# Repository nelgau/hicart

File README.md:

# Home Invader 64

This is a present for an old friend!

## Prerequisites

Get these taps:

    $ brew tap nelgau/fpga
    $ brew tap riscv-software-src/riscv

Install the following packages:

    $ brew install --HEAD yosys
    $ brew install --HEAD nelgau/fpga/nextpnr-ecp5
    $ brew install --HEAD nelgau/fpga/ecpprog
    $ brew install riscv-software-src/riscv/riscv-tools
    $ brew install icarus-verilog

Note: Building `nextpnr-ecp5` takes approximately 11 minutes on an M1 MacBook Pro.

Build a recent Python with shared object support (for cocotb) using pyenv:

    $ PYTHON_CONFIGURE_OPTS="--enable-shared" pyenv install 3.10.6

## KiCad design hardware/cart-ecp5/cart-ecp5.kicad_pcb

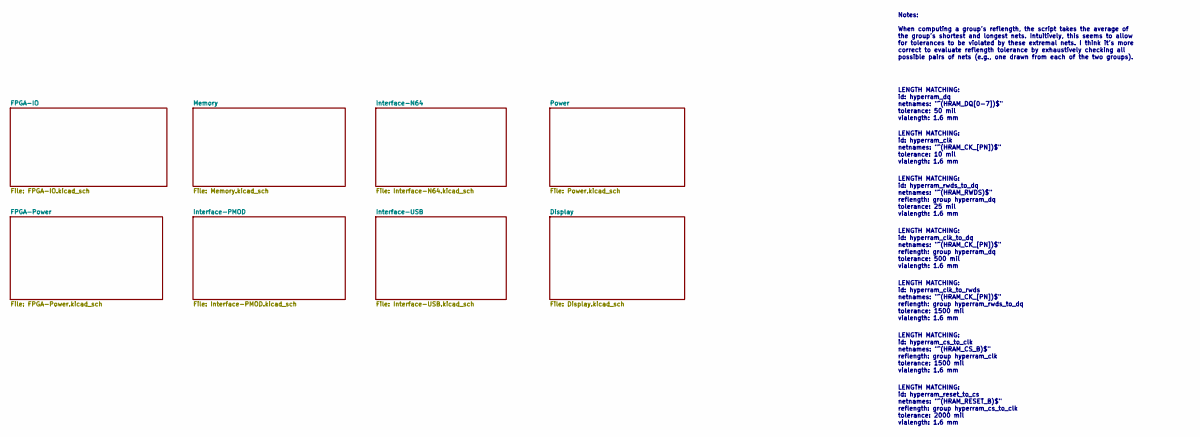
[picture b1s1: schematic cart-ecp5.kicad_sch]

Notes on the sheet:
LENGTH MATCHING: id: hyperram_reset_to_cs netnames: "^(HRAM_RESET_B)$" reflength: group hyperram_cs_to_clk tolerance: 2000 mil vialength: 1.6 mm
LENGTH MATCHING: id: hyperram_clk_to_dq netnames: "^(HRAM_CK_[PN])$" reflength: group hyperram_dq tolerance: 500 mil vialength: 1.6 mm
LENGTH MATCHING: id: hyperram_clk netnames: "^(HRAM_CK_[PN])$" tolerance: 10 mil vialength: 1.6 mm
LENGTH MATCHING: id: hyperram_dq netnames: "^(HRAM_DQ[0-7])$" tolerance: 50 mil vialength: 1.6 mm
LENGTH MATCHING: id: hyperram_clk_to_rwds netnames: "^(HRAM_CK_[PN])$" reflength: group hyperram_rwds_to_dq tolerance: 1500 mil vialength: 1.6 mm
LENGTH MATCHING: id: hyperram_cs_to_clk netnames: "^(HRAM_CS_B)$" reflength: group hyperram_clk tolerance: 1500 mil vialength: 1.6 mm
LENGTH MATCHING: id: hyperram_rwds_to_dq netnames: "^(HRAM_RWDS)$" reflength: group hyperram_dq tolerance: 25 mil vialength: 1.6 mm
Notes: When computing a group's reflength, the script takes the average of the group's shortest and longest nets. Intuitively, this seems to allow for tolerances to be violated by these extremal nets. I think it's more correct to evaluate reflength tolerance by exhaustively checking all possible pa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

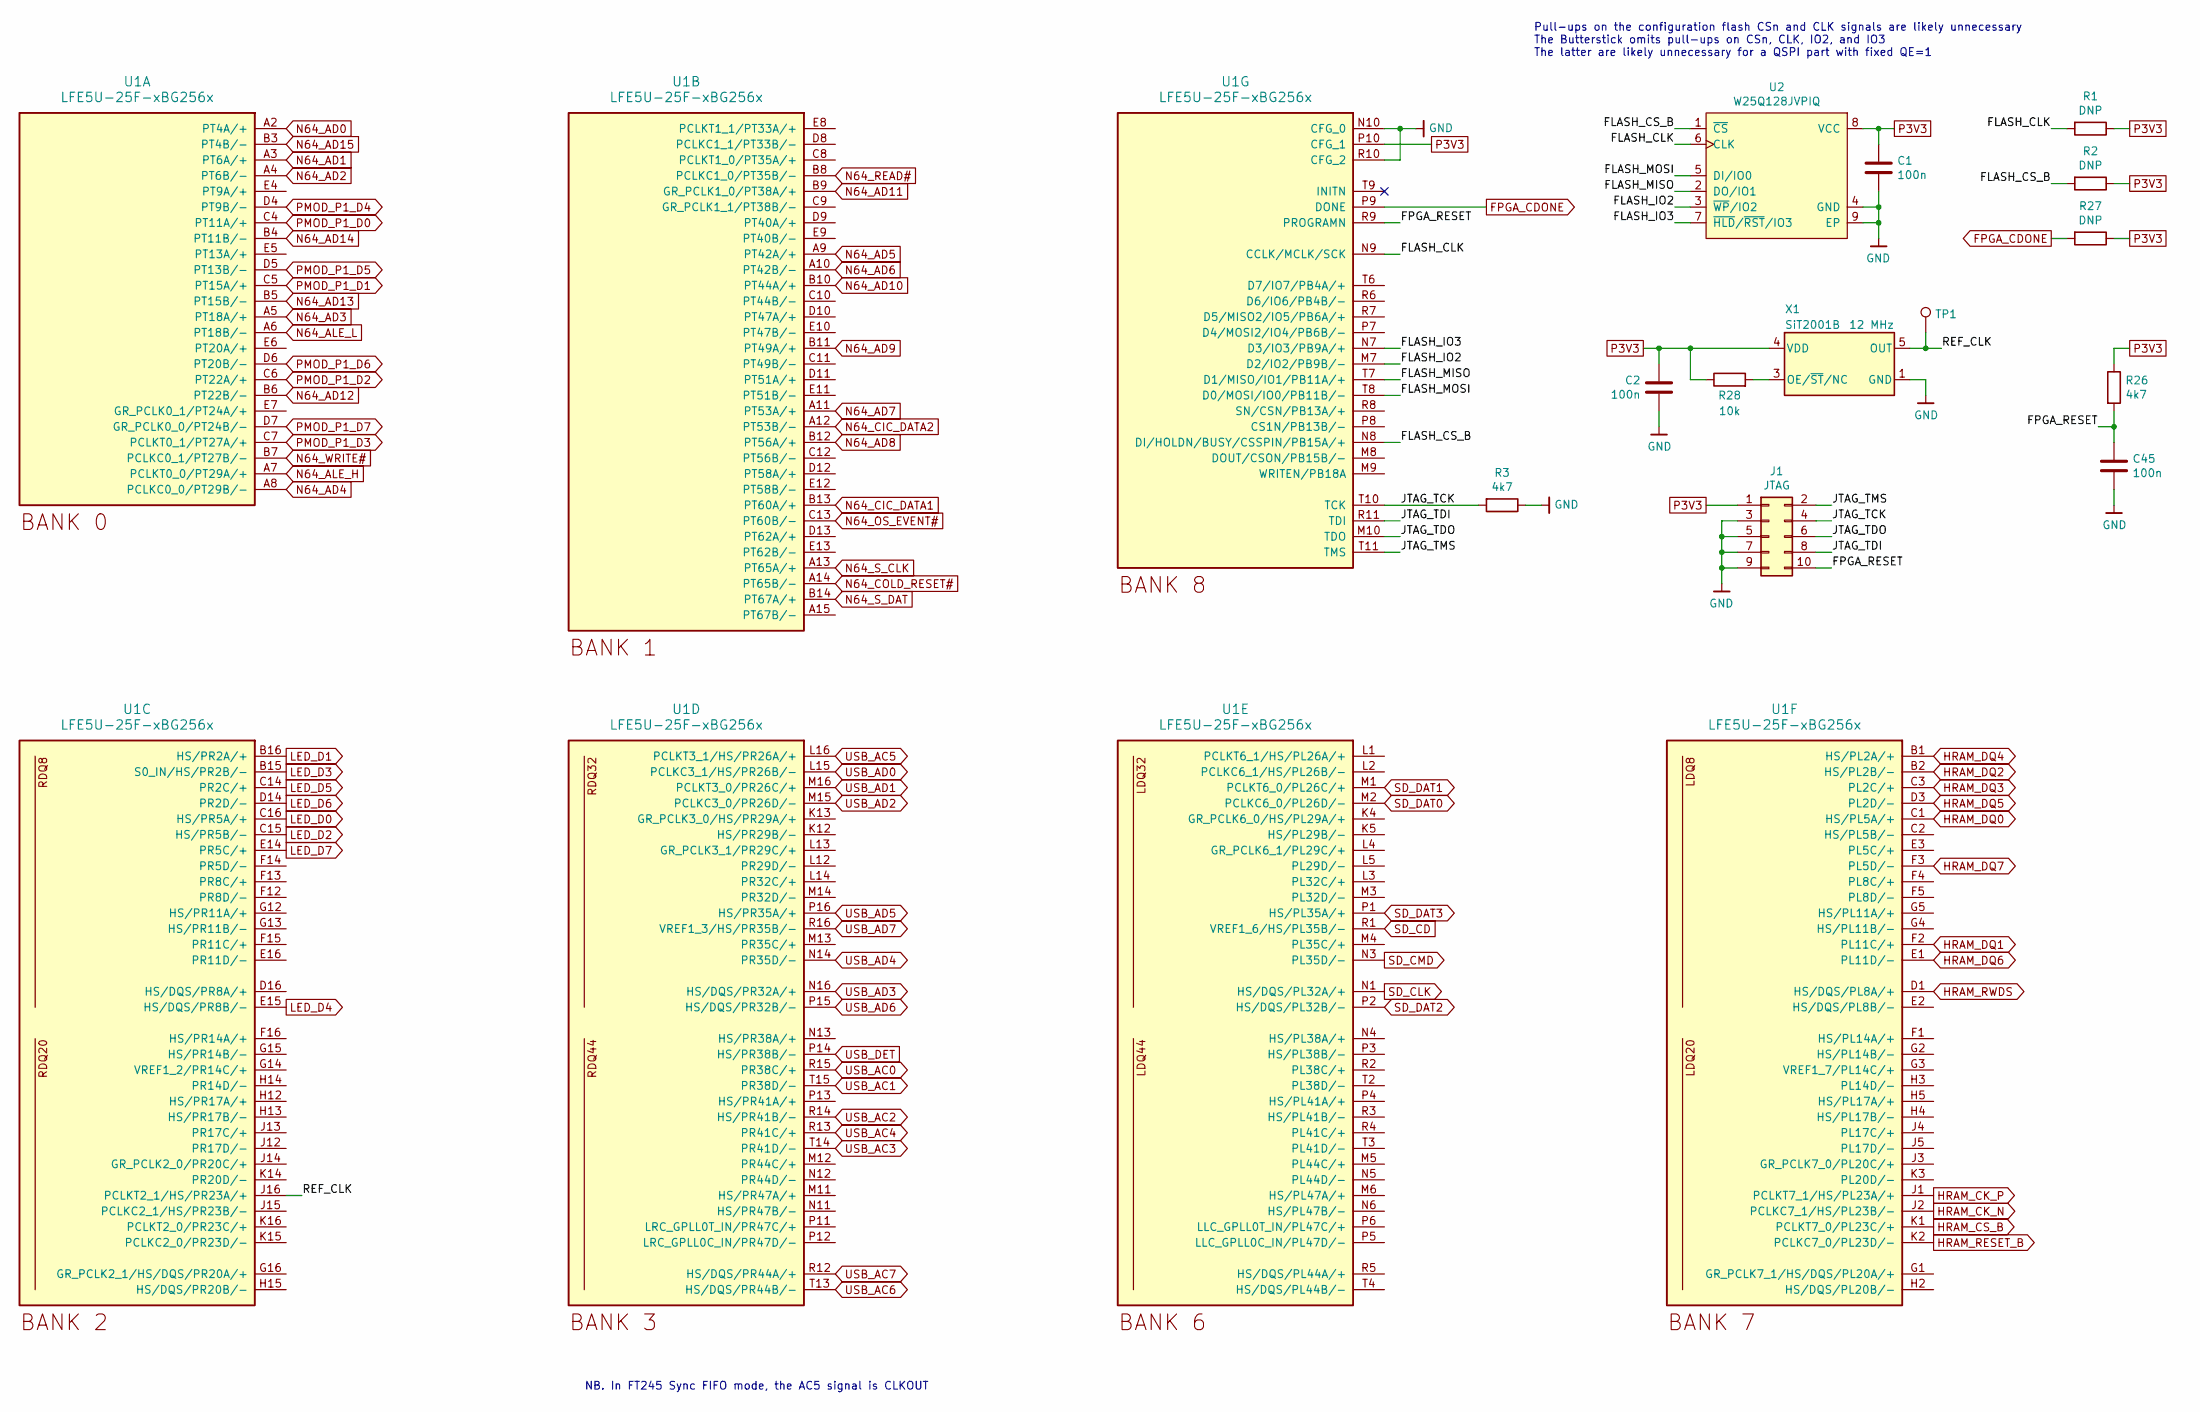
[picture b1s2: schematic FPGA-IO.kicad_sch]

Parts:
C1, C2, C45: 100n; C_0402_1005Metric; MPN CL05B104KO5NNNC
J1: JTAG; Samtec_FTSH-105-XX-X-DV-Mating; MPN FTSH-105-01-L-DV-K
R1, R2, R27: DNP; R_0402_1005Metric
R3, R26: 4k7; R_0402_1005Metric; MPN RC0402FR-074K7L
R28: 10k; R_0402_1005Metric; MPN RC0402FR-0710KL
TP1: TestPoint; TestPoint_Pad_D1.0mm
U1: LFE5U-25F-xBG256x; LFE5U-25F_BGA-256_14.0x14.0mm_Layout16x16_P0.8mm_Pad0.35mm; MPN LFE5U-25F-xBG256x
U2: W25Q128JVPIQ; WSON-8-1EP_6x5mm_P1.27mm_EP3.4x4mm; MPN W25Q128JVPIQ
X1: SiT2001B; SOT-23-5; MPN SiT2001BI-S2-33E-12.000000G

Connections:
/FPGA-IO/FLASH_CLK: R1.2, U1.N9 (CCLK/MCLK/SCK), U2.6 (CLK)
/FPGA-IO/FLASH_CS_B: R2.2, U1.N8 (DI/HOLDN/BUSY/CSSPIN/PB15A/+), U2.1 (~CS)
/FPGA-IO/FLASH_IO2: U1.M7 (D2/IO2/PB9B/-), U2.3 (~WP/IO2)
/FPGA-IO/FLASH_IO3: U1.N7 (D3/IO3/PB9A/+), U2.7 (~HLD/~RST/IO3)
/FPGA-IO/FLASH_MISO: U1.T7 (D1/MISO/IO1/PB11A/+), U2.2 (DO/IO1)
/FPGA-IO/FLASH_MOSI: U1.T8 (D0/MOSI/IO0/PB11B/-), U2.5 (DI/IO0)
/FPGA-IO/FPGA_RESET: C45.1, J1.10, R26.2, U1.R9 (PROGRAMN)
/FPGA-IO/JTAG_TCK: J1.4, R3.2, U1.T10 (TCK)
/FPGA-IO/JTAG_TDI: J1.8, U1.R11 (TDI)
/FPGA-IO/JTAG_TDO: J1.6, U1.M10 (TDO)
/FPGA-IO/JTAG_TMS: J1.2, U1.T11 (TMS)
/FPGA-IO/REF_CLK: TP1.1, U1.J16 (PCLKT2_1/HS/PR23A/+), X1.5 (OUT)
FPGA_CDONE: R27.2, U1.P9 (DONE); also elsewhere on the board
GND: C1.2, C2.2, C45.2, J1.3, J1.5, J1.7, J1.9, R3.1, U1.N10 (CFG_0), U1.R10 (CFG_2), U2.4 (GND), U2.9 (EP), X1.1 (GND); also elsewhere on the board
HRAM_CK_N: U1.J2 (PCLKC7_1/HS/PL23B/-); also elsewhere on the board
HRAM_CK_P: U1.J1 (PCLKT7_1/HS/PL23A/+); also elsewhere on the board
HRAM_CS_B: U1.K1 (PCLKT7_0/PL23C/+); also elsewhere on the board
HRAM_DQ0: U1.C1 (HS/PL5A/+); also elsewhere on the board
HRAM_DQ1: U1.F2 (PL11C/+); also elsewhere on the board
HRAM_DQ2: U1.B2 (HS/PL2B/-); also elsewhere on the board
HRAM_DQ3: U1.C3 (PL2C/+); also elsewhere on the board
HRAM_DQ4: U1.B1 (HS/PL2A/+); also elsewhere on the board
HRAM_DQ5: U1.D3 (PL2D/-); also elsewhere on the board
HRAM_DQ6: U1.E1 (PL11D/-); also elsewhere on the board
HRAM_DQ7: U1.F3 (PL5D/-); also elsewhere on the board
HRAM_RESET_B: U1.K2 (PCLKC7_0/PL23D/-); also elsewhere on the board
HRAM_RWDS: U1.D1 (HS/DQS/PL8A/+); also elsewhere on the board
LED_D0: U1.C16 (HS/PR5A/+); also elsewhere on the board
LED_D1: U1.B16 (HS/PR2A/+); also elsewhere on the board
LED_D2: U1.C15 (HS/PR5B/-); also elsewhere on the board
LED_D3: U1.B15 (S0_IN/HS/PR2B/-); also elsewhere on the board
LED_D4: U1.E15 (HS/DQS/PR8B/-); also elsewhere on the board
LED_D5: U1.C14 (PR2C/+); also elsewhere on the board
LED_D6: U1.D14 (PR2D/-); also elsewhere on the board
LED_D7: U1.E14 (PR5C/+); also elsewhere on the board
N64_AD0: U1.A2 (PT4A/+); also elsewhere on the board
N64_AD1: U1.A3 (PT6A/+); also elsewhere on the board
N64_AD2: U1.A4 (PT6B/-); also elsewhere on the board
N64_AD3: U1.A5 (PT18A/+); also elsewhere on the board
N64_AD4: U1.A8 (PCLKC0_0/PT29B/-); also elsewhere on the board
N64_AD5: U1.A9 (PT42A/+); also elsewhere on the board
N64_AD6: U1.A10 (PT42B/-); also elsewhere on the board
N64_AD7: U1.A11 (PT53A/+); also elsewhere on the board
N64_AD8: U1.B12 (PT56A/+); also elsewhere on the board
N64_AD9: U1.B11 (PT49A/+); also elsewhere on the board
N64_AD10: U1.B10 (PT44A/+); also elsewhere on the board
N64_AD11: U1.B9 (GR_PCLK1_0/PT38A/+); also elsewhere on the board
N64_AD12: U1.B6 (PT22B/-); also elsewhere on the board
N64_AD13: U1.B5 (PT15B/-); also elsewhere on the board
N64_AD14: U1.B4 (PT11B/-); also elsewhere on the board
N64_AD15: U1.B3 (PT4B/-); also elsewhere on the board
N64_ALE_H: U1.A7 (PCLKT0_0/PT29A/+); also elsewhere on the board
N64_ALE_L: U1.A6 (PT18B/-); also elsewhere on the board
N64_CIC_DATA1: U1.B13 (PT60A/+); also elsewhere on the board
N64_CIC_DATA2: U1.A12 (PT53B/-); also elsewhere on the board
N64_COLD_RESET#: U1.A14 (PT65B/-); also elsewhere on the board
N64_OS_EVENT#: U1.C13 (PT60B/-); also elsewhere on the board
N64_READ#: U1.B8 (PCLKC1_0/PT35B/-); also elsewhere on the board
N64_S_CLK: U1.A13 (PT65A/+); also elsewhere on the board
N64_S_DAT: U1.B14 (PT67A/+); also elsewhere on the board
N64_WRITE#: U1.B7 (PCLKC0_1/PT27B/-); also elsewhere on the board
unnamed: R28.2, X1.3 (OE/~ST/NC)
P3V3: C1.1, C2.1, J1.1, R1.1, R2.1, R26.1, R27.1, R28.1, U1.P10 (CFG_1), U2.8 (VCC), X1.4 (VDD); also elsewhere on the board
PMOD_P1_D0: U1.C4 (PT11A/+); also elsewhere on the board
PMOD_P1_D1: U1.C5 (PT15A/+); also elsewhere on the board
PMOD_P1_D2: U1.C6 (PT22A/+); also elsewhere on the board
PMOD_P1_D3: U1.C7 (PCLKT0_1/PT27A/+); also elsewhere on the board
PMOD_P1_D4: U1.D4 (PT9B/-); also elsewhere on the board
PMOD_P1_D5: U1.D5 (PT13B/-); also elsewhere on the board
PMOD_P1_D6: U1.D6 (PT20B/-); also elsewhere on the board
PMOD_P1_D7: U1.D7 (GR_PCLK0_0/PT24B/-); also elsewhere on the board
SD_CD: U1.R1 (VREF1_6/HS/PL35B/-); also elsewhere on the board
SD_CLK: U1.N1 (HS/DQS/PL32A/+); also elsewhere on the board
SD_CMD: U1.N3 (PL35D/-); also elsewhere on the board
SD_DAT0: U1.M2 (PCLKC6_0/PL26D/-); also elsewhere on the board
SD_DAT1: U1.M1 (PCLKT6_0/PL26C/+); also elsewhere on the board
SD_DAT2: U1.P2 (HS/DQS/PL32B/-); also elsewhere on the board
SD_DAT3: U1.P1 (HS/PL35A/+); also elsewhere on the board
USB_AC0: U1.R15 (PR38C/+); also elsewhere on the board
USB_AC1: U1.T15 (PR38D/-); also elsewhere on the board
USB_AC2: U1.R14 (HS/PR41B/-); also elsewhere on the board
USB_AC3: U1.T14 (PR41D/-); also elsewhere on the board
USB_AC4: U1.R13 (PR41C/+); also elsewhere on the board
USB_AC5: U1.L16 (PCLKT3_1/HS/PR26A/+); also elsewhere on the board
USB_AC6: U1.T13 (HS/DQS/PR44B/-); also elsewhere on the board
USB_AC7: U1.R12 (HS/DQS/PR44A/+); also elsewhere on the board
USB_AD0: U1.L15 (PCLKC3_1/HS/PR26B/-); also elsewhere on the board
USB_AD1: U1.M16 (PCLKT3_0/PR26C/+); also elsewhere on the board
USB_AD2: U1.M15 (PCLKC3_0/PR26D/-); also elsewhere on the board
USB_AD3: U1.N16 (HS/DQS/PR32A/+); also elsewhere on the board
USB_AD4: U1.N14 (PR35D/-); also elsewhere on the board
USB_AD5: U1.P16 (HS/PR35A/+); also elsewhere on the board
USB_AD6: U1.P15 (HS/DQS/PR32B/-); also elsewhere on the board
USB_AD7: U1.R16 (VREF1_3/HS/PR35B/-); also elsewhere on the board
USB_DET: U1.P14 (HS/PR38B/-); also elsewhere on the board

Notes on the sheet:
NB. In FT245 Sync FIFO mode, the AC5 signal is CLKOUT
Pull-ups on the configuration flash CSn and CLK signals are likely unnecessary The Butterstick omits pull-ups on CSn, CLK, IO2, and IO3 The latter are likely unnecessary for a QSPI part with fixed QE=1

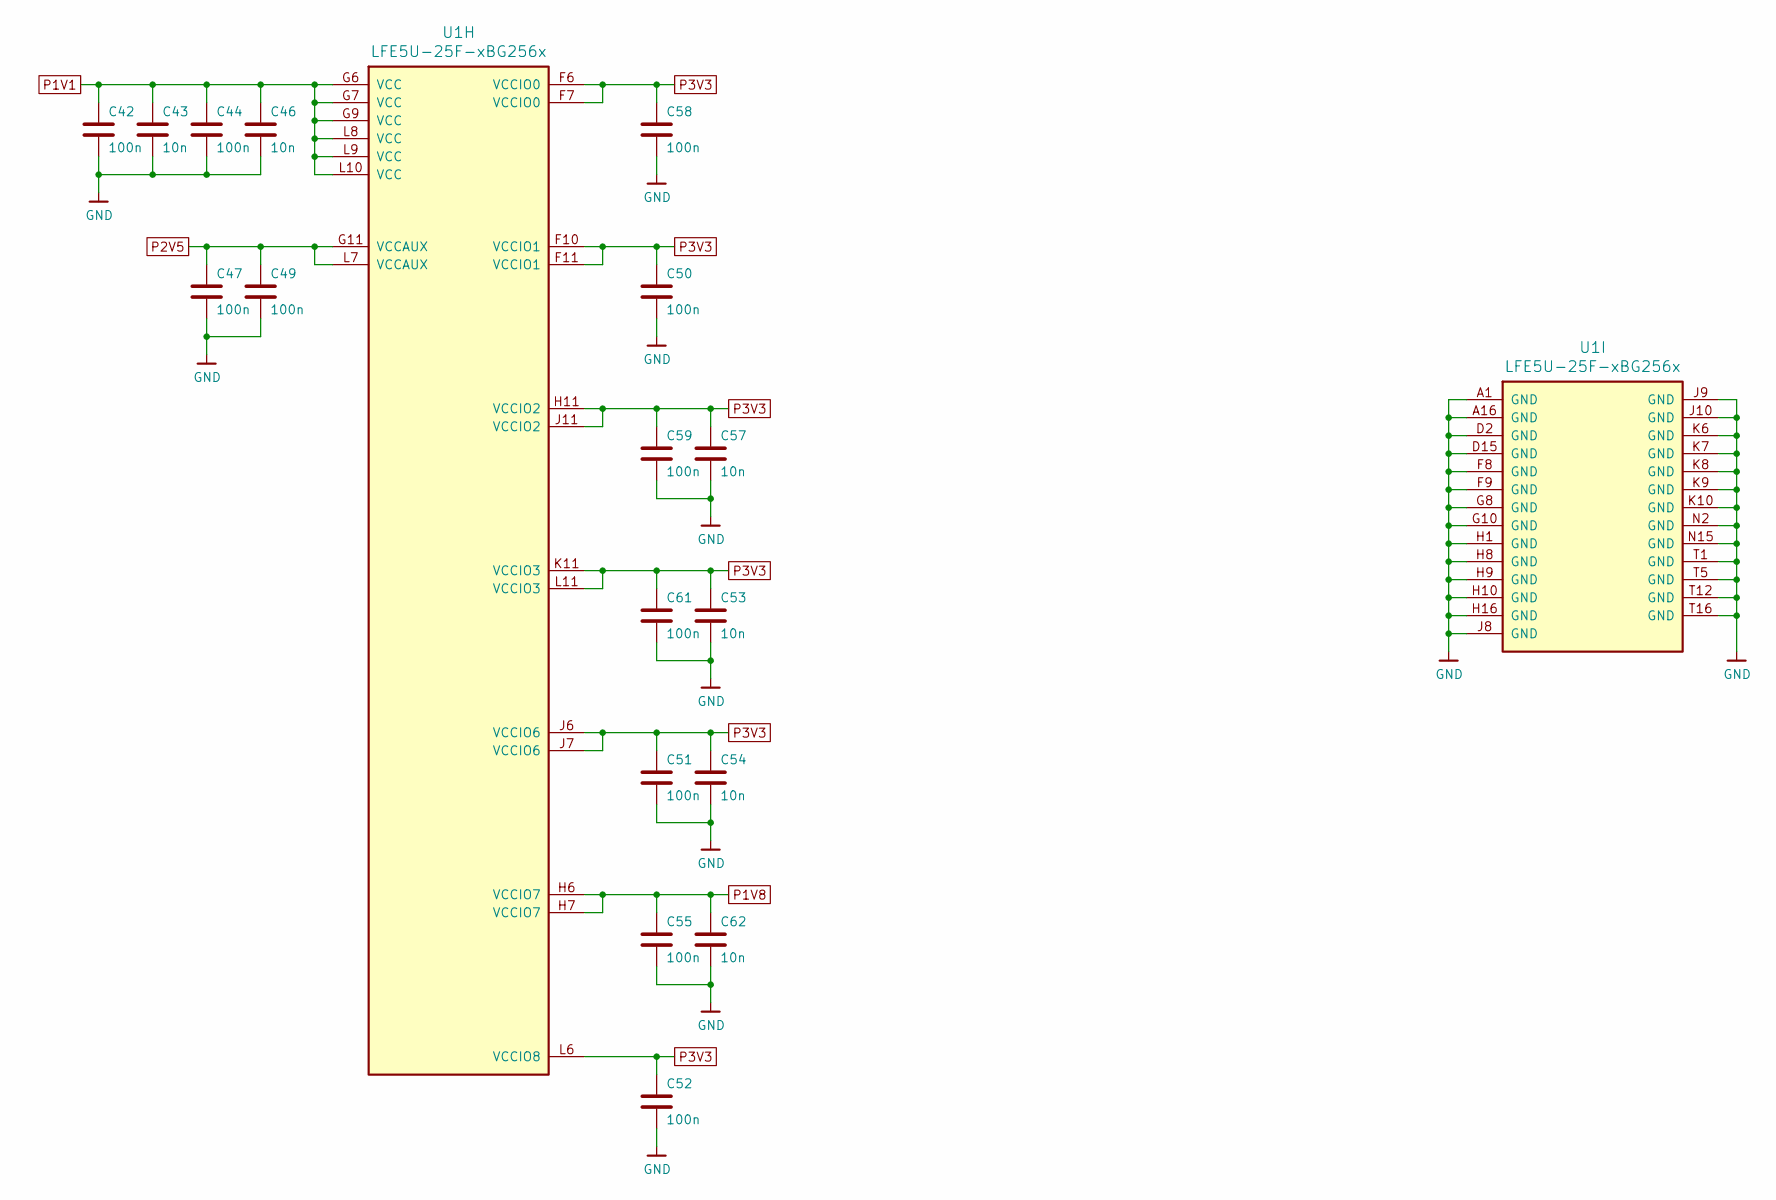
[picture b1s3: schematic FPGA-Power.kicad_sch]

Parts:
C42, C44, C47, C49, C50, C51, C52, C55, C58, C59, C61: 100n; C_0402_1005Metric; MPN CL05B104KO5NNNC
C43, C46, C53, C54, C57, C62: 10n; C_0402_1005Metric; MPN CL05B103KB5NNNC
U1: LFE5U-25F-xBG256x; LFE5U-25F_BGA-256_14.0x14.0mm_Layout16x16_P0.8mm_Pad0.35mm; MPN LFE5U-25F-xBG256x

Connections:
GND: C42.2, C43.2, C44.2, C46.2, C47.2, C49.2, C50.2, C51.2, C52.2, C53.2, C54.2, C55.2, C57.2, C58.2, C59.2, C61.2, C62.2, U1.A1 (GND), U1.A16 (GND), U1.D2 (GND), U1.D15 (GND), U1.F8 (GND), U1.F9 (GND), U1.G8 (GND), U1.G10 (GND), U1.H1 (GND), U1.H8 (GND), U1.H9 (GND), U1.H10 (GND), U1.H16 (GND), U1.J8 (GND), U1.J9 (GND), U1.J10 (GND), U1.K6 (GND), U1.K7 (GND), U1.K8 (GND), U1.K9 (GND), U1.K10 (GND), U1.N2 (GND), U1.N15 (GND), U1.T1 (GND), U1.T5 (GND), U1.T12 (GND), U1.T16 (GND); also elsewhere on the board
P1V1: C42.1, C43.1, C44.1, C46.1, U1.G6 (VCC), U1.G7 (VCC), U1.G9 (VCC), U1.L8 (VCC), U1.L9 (VCC), U1.L10 (VCC); also elsewhere on the board
P1V8: C55.1, C62.1, U1.H6 (VCCIO7), U1.H7 (VCCIO7); also elsewhere on the board
P2V5: C47.1, C49.1, U1.G11 (VCCAUX), U1.L7 (VCCAUX); also elsewhere on the board
P3V3: C50.1, C51.1, C52.1, C53.1, C54.1, C57.1, C58.1, C59.1, C61.1, U1.F6 (VCCIO0), U1.F7 (VCCIO0), U1.F10 (VCCIO1), U1.F11 (VCCIO1), U1.H11 (VCCIO2), U1.J6 (VCCIO6), U1.J7 (VCCIO6), U1.J11 (VCCIO2), U1.K11 (VCCIO3), U1.L6 (VCCIO8), U1.L11 (VCCIO3); also elsewhere on the board

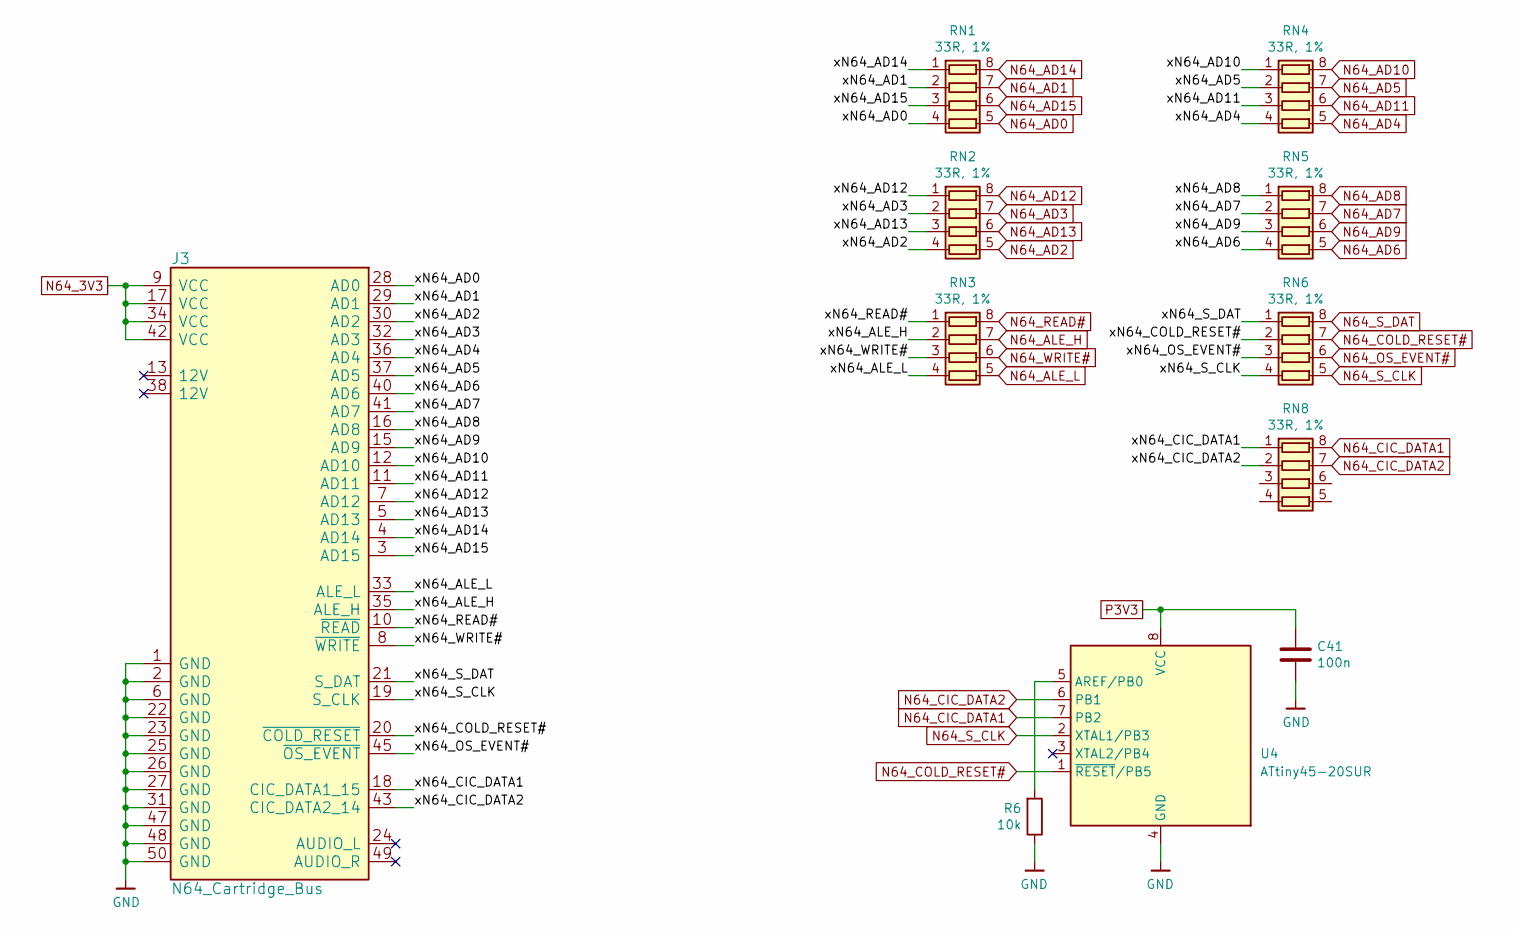
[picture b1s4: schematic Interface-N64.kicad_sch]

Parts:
C41: 100n; C_0402_1005Metric; MPN CL05B104KO5NNNC
J3: N64_Cartridge_Bus; N64_Cartridge_Edge
R6: 10k; R_0402_1005Metric; MPN RC0402FR-0710KL
RN1, RN2, RN3, RN4, RN5, RN6, RN8: 33R, 1%; R_Array_Convex_4x0603; MPN YC164-FR-0733RL
U4: ATtiny45-20SUR; SOIC-8W_5.3x5.3mm_P1.27mm; MPN ATTINY45-20SUR

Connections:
/Interface-N64/xN64_AD0: J3.28 (AD0), RN1.4 (R4.1)
/Interface-N64/xN64_AD1: J3.29 (AD1), RN1.2 (R2.1)
/Interface-N64/xN64_AD2: J3.30 (AD2), RN2.4 (R4.1)
/Interface-N64/xN64_AD3: J3.32 (AD3), RN2.2 (R2.1)
/Interface-N64/xN64_AD4: J3.36 (AD4), RN4.4 (R4.1)
/Interface-N64/xN64_AD5: J3.37 (AD5), RN4.2 (R2.1)
/Interface-N64/xN64_AD6: J3.40 (AD6), RN5.4 (R4.1)
/Interface-N64/xN64_AD7: J3.41 (AD7), RN5.2 (R2.1)
/Interface-N64/xN64_AD8: J3.16 (AD8), RN5.1 (R1.1)
/Interface-N64/xN64_AD9: J3.15 (AD9), RN5.3 (R3.1)
/Interface-N64/xN64_AD10: J3.12 (AD10), RN4.1 (R1.1)
/Interface-N64/xN64_AD11: J3.11 (AD11), RN4.3 (R3.1)
/Interface-N64/xN64_AD12: J3.7 (AD12), RN2.1 (R1.1)
/Interface-N64/xN64_AD13: J3.5 (AD13), RN2.3 (R3.1)
/Interface-N64/xN64_AD14: J3.4 (AD14), RN1.1 (R1.1)
/Interface-N64/xN64_AD15: J3.3 (AD15), RN1.3 (R3.1)
/Interface-N64/xN64_ALE_H: J3.35 (ALE_H), RN3.2 (R2.1)
/Interface-N64/xN64_ALE_L: J3.33 (ALE_L), RN3.4 (R4.1)
/Interface-N64/xN64_CIC_DATA1: J3.18 (CIC_DATA1_15), RN8.1 (R1.1)
/Interface-N64/xN64_CIC_DATA2: J3.43 (CIC_DATA2_14), RN8.2 (R2.1)
/Interface-N64/xN64_COLD_RESET#: J3.20 (~COLD_RESET), RN6.2 (R2.1)
/Interface-N64/xN64_OS_EVENT#: J3.45 (~OS_EVENT), RN6.3 (R3.1)
/Interface-N64/xN64_READ#: J3.10 (~READ), RN3.1 (R1.1)
/Interface-N64/xN64_S_CLK: J3.19 (S_CLK), RN6.4 (R4.1)
/Interface-N64/xN64_S_DAT: J3.21 (S_DAT), RN6.1 (R1.1)
/Interface-N64/xN64_WRITE#: J3.8 (~WRITE), RN3.3 (R3.1)
GND: C41.2, J3.1 (GND), J3.2 (GND), J3.6 (GND), J3.22 (GND), J3.23 (GND), J3.25 (GND), J3.26 (GND), J3.27 (GND), J3.31 (GND), J3.47 (GND), J3.48 (GND), J3.50 (GND), R6.1, U4.4 (GND); also elsewhere on the board
N64_3V3: J3.9 (VCC), J3.17 (VCC), J3.34 (VCC), J3.42 (VCC); also elsewhere on the board
N64_AD0: RN1.5 (R4.2); also elsewhere on the board
N64_AD1: RN1.7 (R2.2); also elsewhere on the board
N64_AD2: RN2.5 (R4.2); also elsewhere on the board
N64_AD3: RN2.7 (R2.2); also elsewhere on the board
N64_AD4: RN4.5 (R4.2); also elsewhere on the board
N64_AD5: RN4.7 (R2.2); also elsewhere on the board
N64_AD6: RN5.5 (R4.2); also elsewhere on the board
N64_AD7: RN5.7 (R2.2); also elsewhere on the board
N64_AD8: RN5.8 (R1.2); also elsewhere on the board
N64_AD9: RN5.6 (R3.2); also elsewhere on the board
N64_AD10: RN4.8 (R1.2); also elsewhere on the board
N64_AD11: RN4.6 (R3.2); also elsewhere on the board
N64_AD12: RN2.8 (R1.2); also elsewhere on the board
N64_AD13: RN2.6 (R3.2); also elsewhere on the board
N64_AD14: RN1.8 (R1.2); also elsewhere on the board
N64_AD15: RN1.6 (R3.2); also elsewhere on the board
N64_ALE_H: RN3.7 (R2.2); also elsewhere on the board
N64_ALE_L: RN3.5 (R4.2); also elsewhere on the board
N64_CIC_DATA1: RN8.8 (R1.2), U4.7 (PB2); also elsewhere on the board
N64_CIC_DATA2: RN8.7 (R2.2), U4.6 (PB1); also elsewhere on the board
N64_COLD_RESET#: RN6.7 (R2.2), U4.1 (~RESET/PB5); also elsewhere on the board
N64_OS_EVENT#: RN6.6 (R3.2); also elsewhere on the board
N64_READ#: RN3.8 (R1.2); also elsewhere on the board
N64_S_CLK: RN6.5 (R4.2), U4.2 (XTAL1/PB3); also elsewhere on the board
N64_S_DAT: RN6.8 (R1.2); also elsewhere on the board
N64_WRITE#: RN3.6 (R3.2); also elsewhere on the board
unnamed: R6.2, U4.5 (AREF/PB0)
P3V3: C41.1, U4.8 (VCC); also elsewhere on the board

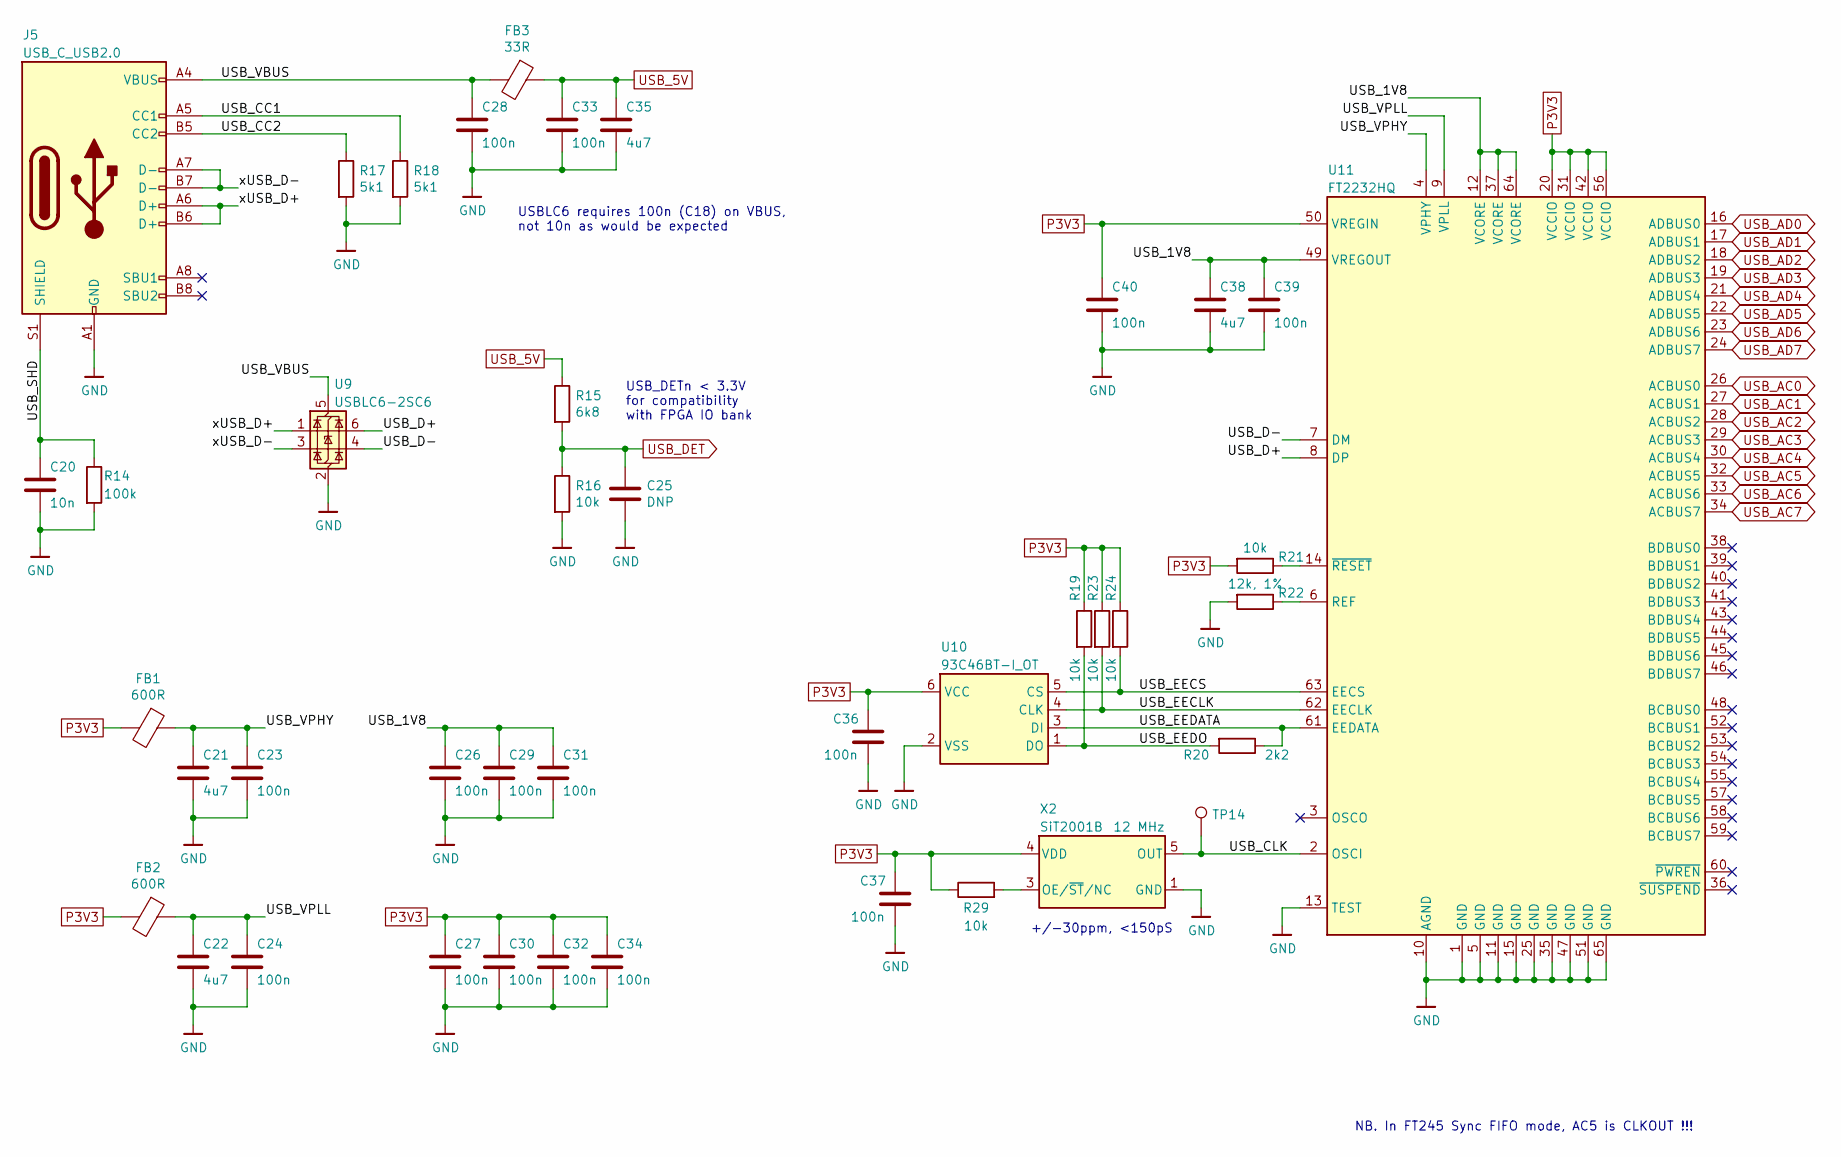
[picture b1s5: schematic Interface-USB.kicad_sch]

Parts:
C20: 10n; C_0402_1005Metric; MPN CL05B103KB5NNNC
C21, C22, C35, C38: 4u7; C_0402_1005Metric; MPN CL05A475KP5NRNC
C23, C24, C26, C27, C28, C29, C30, C31, C32, C33, C34, C36, C37, C39, C40: 100n; C_0402_1005Metric; MPN CL05B104KO5NNNC
C25: DNP; C_0402_1005Metric
FB1, FB2: 600R; L_0402_1005Metric; MPN BLM15PX601SN1D
FB3: 33R; L_0402_1005Metric; MPN MPZ1005S330HT000
J5: USB_C_USB2.0; USB_C_Receptacle_HRO_TYPE-C-31-M-12; MPN TYPE-C-31-M-12
R14: 100k; R_0402_1005Metric; MPN RC0402FR-07100KL
R15: 6k8; R_0402_1005Metric; MPN RC0402FR-076K8L
R16, R19, R21, R23, R24, R29: 10k; R_0402_1005Metric; MPN RC0402FR-0710KL
R17, R18: 5k1; R_0402_1005Metric; MPN RC0402FR-075K1L
R20: 2k2; R_0402_1005Metric; MPN RC0402FR-072K2L
R22: 12k, 1%; R_0402_1005Metric; MPN RC0402FR-0712KL
TP14: TestPoint; TestPoint_Pad_D1.0mm
U9: USBLC6-2SC6; SOT-23-6; MPN USBLC6-2SC6
U10: 93C46BT-I_OT; SOT-23-6; MPN 93C46BT-I/OT
U11: FT2232HQ; QFN-64-1EP_9x9mm_P0.5mm_EP4.35x4.35mm; MPN FT2232HQ
X2: SiT2001B; SOT-23-5; MPN SiT2001BI-S2-33E-12.000000G

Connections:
/Interface-USB/USB_1V8: C26.1, C29.1, C31.1, C38.1, C39.1, U11.12 (VCORE), U11.37 (VCORE), U11.49 (VREGOUT), U11.64 (VCORE)
/Interface-USB/USB_CC1: J5.A5 (CC1), R18.1
/Interface-USB/USB_CC2: J5.B5 (CC2), R17.1
/Interface-USB/USB_CLK: TP14.1, U11.2 (OSCI), X2.5 (OUT)
/Interface-USB/USB_D+: U9.6 (I/O1), U11.8 (DP)
/Interface-USB/USB_D-: U9.4 (I/O2), U11.7 (DM)
/Interface-USB/USB_EECLK: R23.2, U10.4 (CLK), U11.62 (EECLK)
/Interface-USB/USB_EECS: R24.2, U10.5 (CS), U11.63 (EECS)
/Interface-USB/USB_EEDATA: R20.1, U10.3 (DI), U11.61 (EEDATA)
/Interface-USB/USB_EEDO: R19.2, R20.2, U10.1 (DO)
/Interface-USB/USB_SHD: C20.1, J5.S1 (SHIELD), R14.1
/Interface-USB/USB_VBUS: C28.1, FB3.2, J5.A4 (VBUS), J5.A9 (VBUS), J5.B4 (VBUS), J5.B9 (VBUS), U9.5 (VBUS)
/Interface-USB/USB_VPHY: C21.1, C23.1, FB1.1, U11.4 (VPHY)
/Interface-USB/USB_VPLL: C22.1, C24.1, FB2.1, U11.9 (VPLL)
/Interface-USB/xUSB_D+: J5.A6 (D+), J5.B6 (D+), U9.1 (I/O1)
/Interface-USB/xUSB_D-: J5.A7 (D-), J5.B7 (D-), U9.3 (I/O2)
GND: C20.2, C21.2, C22.2, C23.2, C24.2, C25.2, C26.2, C27.2, C28.2, C29.2, C30.2, C31.2, C32.2, C33.2, C34.2, C35.2, C36.2, C37.2, C38.2, C39.2, C40.2, J5.A1 (GND), J5.A12 (GND), J5.B1 (GND), J5.B12 (GND), R14.2, R16.2, R17.2, R18.2, R22.2, U9.2 (GND), U10.2 (VSS), U11.1 (GND), U11.5 (GND), U11.10 (AGND), U11.11 (GND), U11.13 (TEST), U11.15 (GND), U11.25 (GND), U11.35 (GND), U11.47 (GND), U11.51 (GND), U11.65 (GND), X2.1 (GND); also elsewhere on the board
unnamed: R22.1, U11.6 (REF)
unnamed: R21.1, U11.14 (~RESET)
unnamed: R29.2, X2.3 (OE/~ST/NC)
P3V3: C27.1, C30.1, C32.1, C34.1, C36.1, C37.1, C40.1, FB1.2, FB2.2, R19.1, R21.2, R23.1, R24.1, R29.1, U10.6 (VCC), U11.20 (VCCIO), U11.31 (VCCIO), U11.42 (VCCIO), U11.50 (VREGIN), U11.56 (VCCIO), X2.4 (VDD); also elsewhere on the board
USB_5V: C33.1, C35.1, FB3.1, R15.1; also elsewhere on the board
USB_AC0: U11.26 (ACBUS0); also elsewhere on the board
USB_AC1: U11.27 (ACBUS1); also elsewhere on the board
USB_AC2: U11.28 (ACBUS2); also elsewhere on the board
USB_AC3: U11.29 (ACBUS3); also elsewhere on the board
USB_AC4: U11.30 (ACBUS4); also elsewhere on the board
USB_AC5: U11.32 (ACBUS5); also elsewhere on the board
USB_AC6: U11.33 (ACBUS6); also elsewhere on the board
USB_AC7: U11.34 (ACBUS7); also elsewhere on the board
USB_AD0: U11.16 (ADBUS0); also elsewhere on the board
USB_AD1: U11.17 (ADBUS1); also elsewhere on the board
USB_AD2: U11.18 (ADBUS2); also elsewhere on the board
USB_AD3: U11.19 (ADBUS3); also elsewhere on the board
USB_AD4: U11.21 (ADBUS4); also elsewhere on the board
USB_AD5: U11.22 (ADBUS5); also elsewhere on the board
USB_AD6: U11.23 (ADBUS6); also elsewhere on the board
USB_AD7: U11.24 (ADBUS7); also elsewhere on the board
USB_DET: C25.1, R15.2, R16.1; also elsewhere on the board

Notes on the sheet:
USB_DETn < 3.3V for compatibility with FPGA IO bank
USBLC6 requires 100n (C18) on VBUS, not 10n as would be expected
+/-30ppm, <150pS
NB. In FT245 Sync FIFO mode, AC5 is CLKOUT !!!

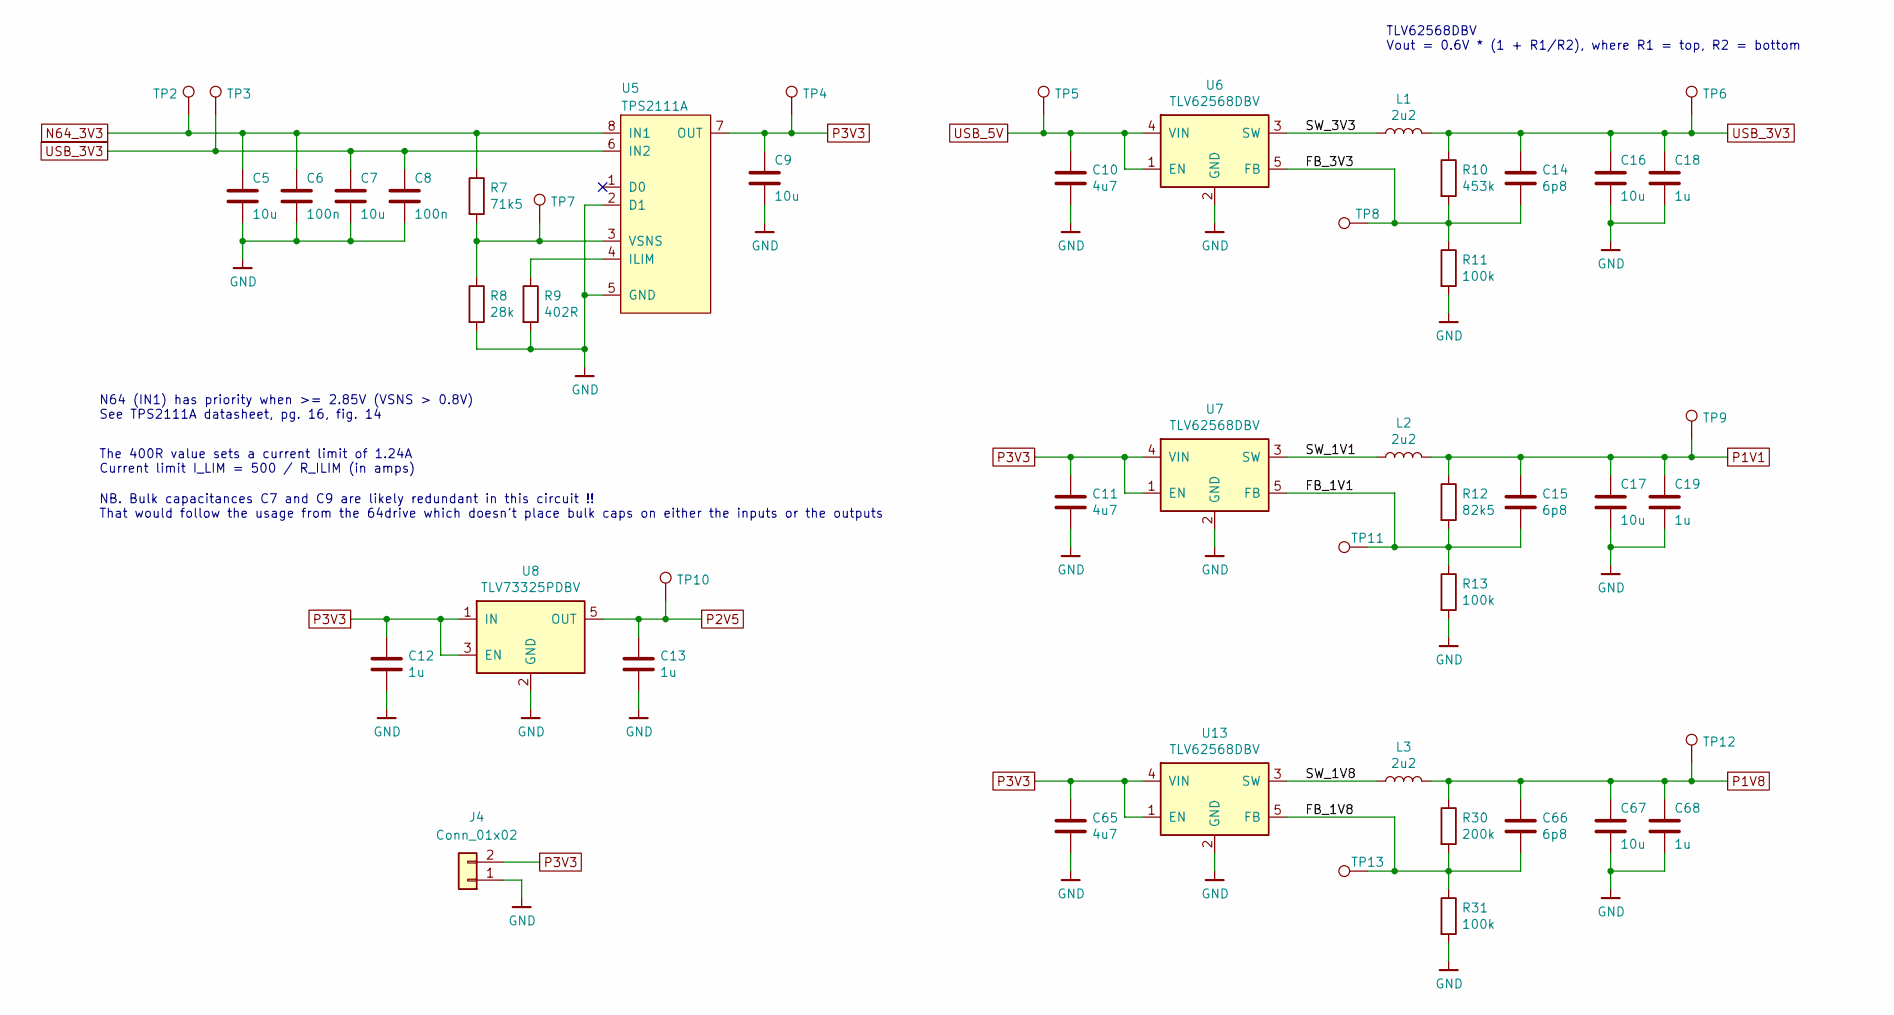
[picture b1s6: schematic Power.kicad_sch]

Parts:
C5, C7, C9, C16, C17, C67: 10u; C_0603_1608Metric; MPN CL10A106MQ8NNND
C6, C8: 100n; C_0402_1005Metric; MPN CL05B104KO5NNNC
C10, C11, C65: 4u7; C_0402_1005Metric; MPN CL05A475KP5NRNC
C12, C13, C18, C19, C68: 1u; C_0402_1005Metric; MPN CL05A105KO5NNNC
C14, C15, C66: 6p8; C_0402_1005Metric; MPN CC0402CRNPO9BN6R8
J4: Conn_01x02; PinHeader_1x02_P2.54mm_Vertical; MPN 22284020
L1, L2, L3: 2u2; L_0805_2012Metric; MPN LQM21PN2R2NGCD
R7: 71k5; R_0402_1005Metric; MPN RC0402FR-0771K5L
R8: 28k; R_0402_1005Metric; MPN RC0402FR-0728KL
R9: 402R; R_0402_1005Metric; MPN RC0402FR-07402RL
R10: 453k; R_0402_1005Metric; MPN RC0402FR-07453KL
R11, R13, R31: 100k; R_0402_1005Metric; MPN RC0402FR-07100KL
R12: 82k5; R_0402_1005Metric; MPN RC0402FR-0782K5L
R30: 200k; R_0402_1005Metric; MPN RC0402FR-07200KL
TP2, TP3, TP4, TP5, TP6, TP7, TP8, TP9, TP10, TP11, TP12, TP13: TestPoint; TestPoint_Pad_D1.0mm
U5: TPS2111A; TSSOP-8_4.4x3mm_P0.65mm; MPN TPS2111APWR
U6, U7, U13: TLV62568DBV; SOT-23-5; MPN TLV62568DBVR
U8: TLV73325PDBV; SOT-23-5; MPN TLV73325PDBVR

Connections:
/Power/FB_1V1: C15.2, R12.2, R13.1, TP11.1, U7.5 (FB)
/Power/FB_1V8: C66.2, R30.2, R31.1, TP13.1, U13.5 (FB)
/Power/FB_3V3: C14.2, R10.2, R11.1, TP8.1, U6.5 (FB)
/Power/SW_1V1: L2.1, U7.3 (SW)
/Power/SW_1V8: L3.1, U13.3 (SW)
/Power/SW_3V3: L1.1, U6.3 (SW)
GND: C5.2, C6.2, C7.2, C8.2, C9.2, C10.2, C11.2, C12.2, C13.2, C16.2, C17.2, C18.2, C19.2, C65.2, C67.2, C68.2, J4.1, R8.2, R9.2, R11.2, R13.2, R31.2, U5.2 (D1), U5.5 (GND), U6.2 (GND), U7.2 (GND), U8.2 (GND), U13.2 (GND); also elsewhere on the board
N64_3V3: C5.1, C6.1, R7.1, TP2.1, U5.8 (IN1); also elsewhere on the board
unnamed: R9.1, U5.4 (ILIM)
unnamed: R7.2, R8.1, TP7.1, U5.3 (VSNS)
P1V1: C15.1, C17.1, C19.1, L2.2, R12.1, TP9.1; also elsewhere on the board
P1V8: C66.1, C67.1, C68.1, L3.2, R30.1, TP12.1; also elsewhere on the board
P2V5: C13.1, TP10.1, U8.5 (OUT); also elsewhere on the board
P3V3: C9.1, C11.1, C12.1, C65.1, J4.2, TP4.1, U5.7 (OUT), U7.1 (EN), U7.4 (VIN), U8.1 (IN), U8.3 (EN), U13.1 (EN), U13.4 (VIN); also elsewhere on the board
USB_3V3: C7.1, C8.1, C14.1, C16.1, C18.1, L1.2, R10.1, TP3.1, TP6.1, U5.6 (IN2)
USB_5V: C10.1, TP5.1, U6.1 (EN), U6.4 (VIN); also elsewhere on the board

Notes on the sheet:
The 400R value sets a current limit of 1.24A Current limit I_LIM = 500 / R_ILIM (in amps)
NB. Bulk capacitances C7 and C9 are likely redundant in this circuit !! That would follow the usage from the 64drive which doesn’t place bulk caps on either the inputs or the outputs
TLV62568DBV Vout = 0.6V * (1 + R1/R2), where R1 = top, R2 = bottom
N64 (IN1) has priority when >= 2.85V (VSNS > 0.8V) See TPS2111A datasheet, pg. 16, fig. 14

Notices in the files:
hardware/fpga-ice40/Display.sch:
Licensed under CERN OHL v.1.2
